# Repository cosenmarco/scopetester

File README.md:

# ScopeTester
An Open Hardware project for a small oscilloscope tester and calibrator with features like the [Hameg HZ-60](https://www.radiomuseum.org/r/hameg_scope_tester_hz_60.html).

## License
This project aims to be "open" in the sense of [Open Hardware](https://en.wikipedia.org/wiki/Open-source_hardware) and [Free Libre Open Source](https://en.wikipedia.org/wiki/Free_and_open-source_software).
The project is made available under the terms of the [Creative Commons license](https://creativecommons.org/licenses/by-sa/4.0/).

## Tools
The harware is developed using [KiCAD](http://kicad-pcb.org/).
Firmware is developed using [MPLAB X](http://www.microchip.com/mplab/mplab-x-ide) and the [XC8 compiler](http://www.microchip.com/mplab/compilers) from Microchip.

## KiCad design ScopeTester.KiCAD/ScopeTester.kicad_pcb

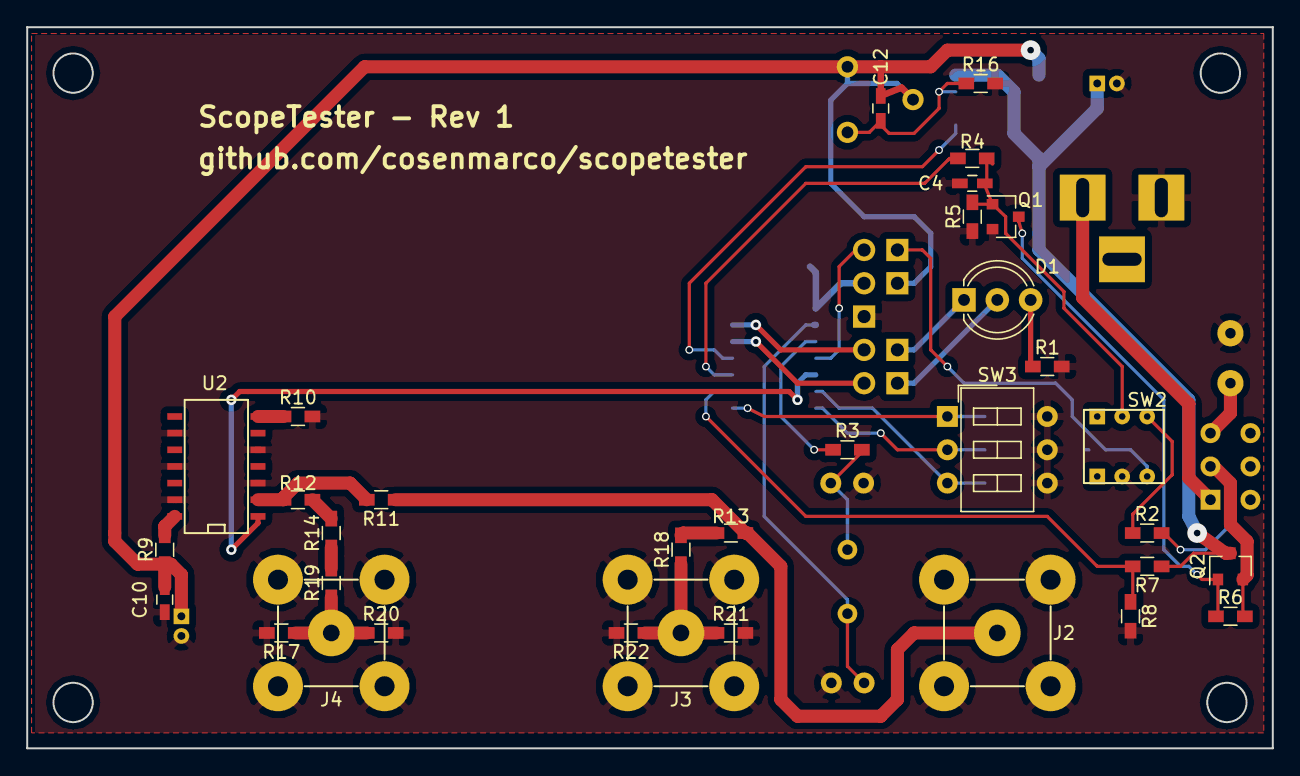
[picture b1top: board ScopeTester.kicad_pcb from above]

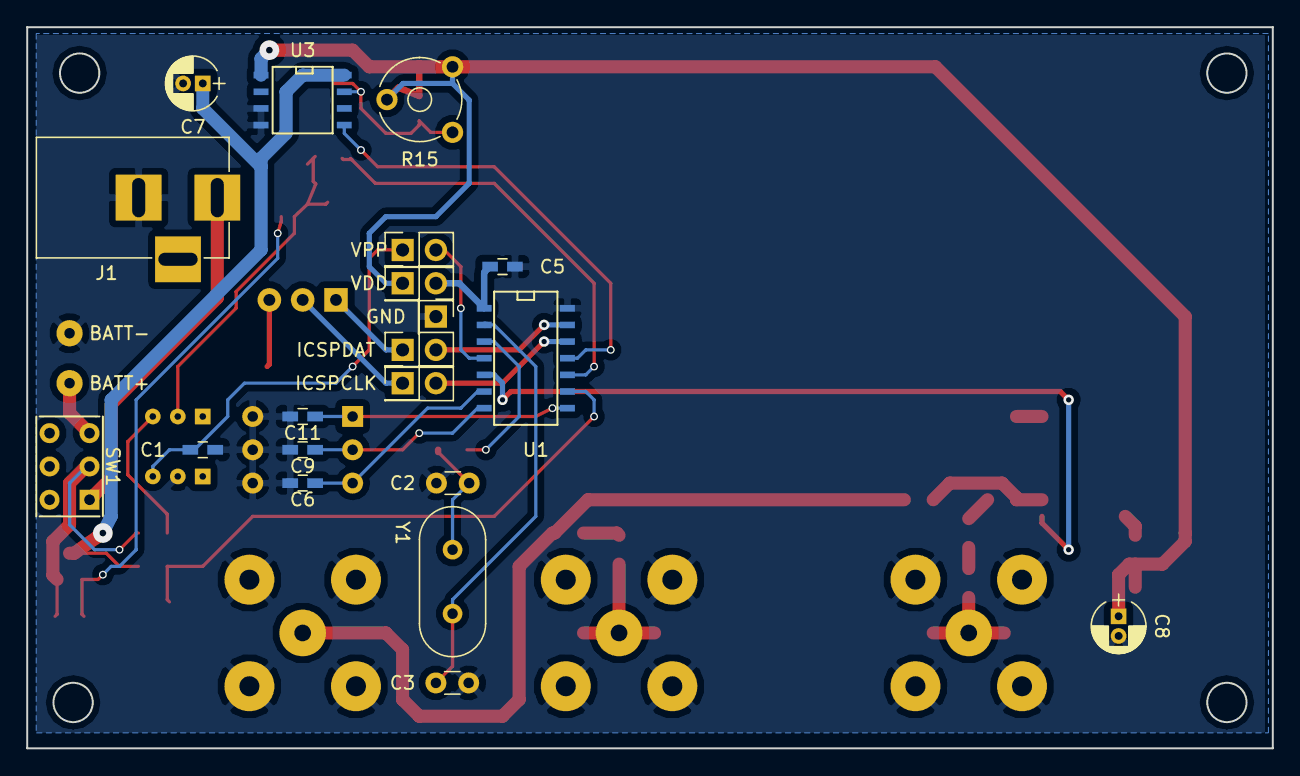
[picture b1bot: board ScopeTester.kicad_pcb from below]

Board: 2 copper layers, 95.0 x 55.0 mm, 55 parts (22 on the bottom side), 37 nets.

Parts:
BATT+: 4xLR6(AA); SolderWirePad_single_0-8mmDrill
BATT-: TEST; SolderWirePad_single_0-8mmDrill
C1: 330nF; C_0603_HandSoldering
C2, C3: 22pF; C_Disc_D3.0mm_W1.6mm_P2.50mm
C4: 0.22µF; C_0603_HandSoldering
C5: 100nF; C_0603_HandSoldering
C6, C9, C11: 0; C_0603_HandSoldering
C7: 3.3µF; CP_Radial_D4.0mm_P1.50mm
C8: 10µF; CP_Radial_D4.0mm_P1.50mm
C10, C12: 0.01µF; C_0603_HandSoldering
D1: ON/ERROR; LED_D5.0mm-3
GND: GND; Pin_Header_Straight_1x01_Pitch2.54mm
ICSPCLK: Jumper; Pin_Header_Straight_2x01_Pitch2.54mm
ICSPDAT: Jumper; Pin_Header_Straight_2x01_Pitch2.54mm
J1: 5VDC; BARREL_JACK
J2: 2.5Vpp; bnc-ci-large
J3: 250mV; bnc-ci-large
J4: 25mVpp into 50 Ohm; bnc-ci-large
Q1: BSS138; SOT-23
Q2: IRLML6401; SOT-23
R1: 560R; R_0603_HandSoldering
R2: 10K; R_0603_HandSoldering
R3: 0R; R_0603_HandSoldering
R4: 5K6; R_0603_HandSoldering
R5, R6: 56K; R_0603_HandSoldering
R7: 33k; R_0603_HandSoldering
R8: 12k; R_0603_HandSoldering
R9, R10: 15R; R_0603_HandSoldering
R11, R18: 150R; R_0603_HandSoldering
R12: 226R; R_0603_HandSoldering
R13: 301R; R_0603_HandSoldering
R14, R19: 1K5; R_0603_HandSoldering
R15: 220K; Potentiometer_Trimmer_Piher_PT-6v_Horizontal
R16: 100K; R_0603_HandSoldering
R17, R20, R21, R22: 100R; R_0603_HandSoldering
SW1: BATTERY/DC; SW_DPDT_Slide_mini
SW2: ON/OFF; DPDT_Button_mini
SW3: FREQ SEL; SW_DIP_x3_W7.62mm_Slide_LowProfile
U1: PIC16F1823-I/ST; SOIC-14_N
U2: 74AC14; SOIC-14_N
U3: TS2951; SOIC-8-N
VDD: Jumper; Pin_Header_Straight_2x01_Pitch2.54mm
VPP: Jumper; Pin_Header_Straight_2x01_Pitch2.54mm
Y1: 8.000Mhz; Crystal_HC49-4H_Vertical

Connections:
ERR: U1.11, U3.5
GND: BATT-.1, C1.2, C2.2, C3.2, C4.2, C5.1, C6.2, C7.2, C8.2, C9.2, C10.2, C11.2, GND.1, J1.2, J2.2, J3.2, J4.2, Q1.2, R1.2, R5.1, R8.2, R10.2, R16.2, R17.2, R20.2, R21.2, R22.2, SW2.5, SW3.4, SW3.5, SW3.6, U1.14, U2.3, U2.5, U2.9, U2.11, U2.13, U3.3, U3.4
unnamed: BATT+.1, SW1.3
unnamed: C2.1, R3.2, Y1.1
unnamed: C3.1, U1.2, Y1.2
unnamed: C4.1, Q1.1, R4.1, R5.2, SW2.2
unnamed: C5.2, U1.1, VDD.2
unnamed: C6.1, SW3.3, U1.6
unnamed: C7.1, Q2.3, R7.1, U3.8
unnamed: C9.1, SW3.2, U1.7
unnamed: C11.1, SW3.1, U1.8
unnamed: C12.2, R15.3, R16.1, U3.7
unnamed: D1.1, ICSPDAT.1
unnamed: D1.2, ICSPCLK.1
unnamed: D1.3, R1.1
unnamed: J1.1, SW1.1
unnamed: J2.1, R11.1, R13.2
unnamed: J3.1, R18.1, R21.1, R22.1
unnamed: J4.1, R17.1, R19.1, R20.1
unnamed: ICSPDAT.2, U1.13
unnamed: ICSPCLK.2, U1.12
unnamed: U1.4, VPP.2
unnamed: Q1.3, Q2.1, R6.1
unnamed: Q2.2, R2.2, R6.2, SW1.2
unnamed: R2.1, SW2.3
unnamed: R3.1, U1.3
unnamed: R9.2, U2.14
unnamed: R10.1, U2.7
unnamed: R11.2, R12.2, U2.2
unnamed: R12.1, R14.2
unnamed: R13.1, R18.2
unnamed: R14.1, R19.2
unnamed: U1.5, U2.1
SENSE: R7.2, R8.1, U1.9
SHUTDOWN: R4.2, U1.10
SWITCH: C1.1, SW2.6, VPP.1
VDD: C8.1, C10.1, C12.1, R9.1, R15.1, R15.2, U3.1, VDD.1

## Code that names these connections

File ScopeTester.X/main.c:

/**
 * Scope Tester
 * Author: https://github.com/cosenmarco
 * License: https://creativecommons.org/licenses/by-sa/4.0/legalcode
 * Processor: PIC16F1823
 * This is the C (Microchip XC8 compiler) source for the project discussed at 
 * http://www.eevblog.com/forum/projects/oscilloscope-tester-like-hameg-hz60/
*/
#include <xc.h>
#include <stdint.h>

// CONFIG1
#pragma config FOSC = HS        // Oscillator Selection (HS Oscillator, High-speed crystal/resonator connected between OSC1 and OSC2 pins)
#pragma config WDTE = OFF       // Watchdog Timer Enable (WDT disabled)
#pragma config PWRTE = ON       // Power-up Timer Enable (PWRT enabled)
#pragma config MCLRE = OFF      // MCLR Pin Function Select (MCLR/VPP pin function is digital input)
#pragma config CP = OFF         // Flash Program Memory Code Protection (Program memory code protection is disabled)
#pragma config CPD = OFF        // Data Memory Code Protection (Data memory code protection is disabled)
#pragma config BOREN = ON       // Brown-out Reset Enable (Brown-out Reset enabled)
#pragma config CLKOUTEN = OFF   // Clock Out Enable (CLKOUT function is disabled. I/O or oscillator function on the CLKOUT pin)
#pragma config IESO = OFF       // Internal/External Switchover (Internal/External Switchover mode is disabled)
#pragma config FCMEN = OFF      // Fail-Safe Clock Monitor Enable (Fail-Safe Clock Monitor is disabled)

// CONFIG2
#pragma config WRT = OFF        // Flash Memory Self-Write Protection (Write protection off)
#pragma config PLLEN = ON       // PLL Enable (4x PLL enabled) -- Fosc will be 32MHz with our 8MHz crystal
#pragma config STVREN = ON      // Stack Overflow/Underflow Reset Enable (Stack Overflow or Underflow will cause a Reset)
#pragma config BORV = LO        // Brown-out Reset Voltage Selection (Brown-out Reset Voltage (Vbor), low trip point selected.)
#pragma config LVP = OFF        // Low-Voltage Programming Enable (Low-voltage programming disabled)

// OUTPUTS
#define LED_GRN LATAbits.LATA0
#define LED_RED LATAbits.LATA1
#define SHUTDOWN LATCbits.LATC0
#define OUT LATCbits.LATC5

// INPUTS
#define ERR PORTAbits.RA2
#define SWITCH PORTAbits.RA3
#define SENSE PORTCbits.C12IN1N
#define FSEL0 PORTCbits.RC2
#define FSEL1 PORTCbits.RC3
#define FSEL2 PORTCbits.RC4

#define SW_PRESSED 0
#define SW_RELEASED 1

#define SHTDN_KEEP_ON 1
#define SHTDN_TURN_OFF 0

#define DC_OUT_LEVEL 0

typedef enum { 
    F_1MHz,
    F_100KHz,
    F_10KHz,
    F_1KHz,
    F_100Hz,
    F_10Hz,
    F_1Hz,
    F_DC
} mode_t;

typedef struct {
    unsigned char prescale;
    unsigned char pr2Value;
    unsigned char ccpr1lValue;
    unsigned char dc1bValue;
} pwm_setup_t;

typedef struct {
    unsigned char prescale;
    unsigned char ccpr1hValue;
    unsigned char ccpr1lValue;
} compare_setup_t;

void turnOnGreenLed(void);
void turnOnRedLed(void);
unsigned readMode(void);
void setupMode(mode_t mode);
void setupPWM(pwm_setup_t setup);
void setupCompare(compare_setup_t setup);
void setupDC(void);
void checkPower(void);

void main(void) {
    
    INTCONbits.GIE = 1; // Enable global interrupt
    INTCONbits.PEIE = 1; // Enable peripheral interrupt
    
    // PORT A configuration
    PORTA = 0;
    ANSELA = 0;
    TRISA = 0b111100; // Input from the TS2951 Error pin and the ON/OFF button
    WPUA = 0b001100; // Weak Pull-up enalbed on ERR and SWITCH inputs
    
    // PORT C configuration
    PORTC = 0;
    ANSELC = 0;
    TRISC = 0b011110; // We use here RC0 for SHUTDOWN and RC5 as the signal OUT
    WPUC = 0b011100; // We want to pull-up all the frequency seletion switches

    OPTION_REGbits.nWPUEN = 0; // Enable Weak Pull-up resistors
   
    SHUTDOWN = SHTDN_KEEP_ON; // Make sure circuit stays ON
    
    // Setup FVR and Comparator for battery voltage sensing
    FVRCON = 0b10000100; // Fixed Voltage Reference is enabled (1x)
    CM1CON0 = 0b10000010; // Enable Comparator (direct, low speed, hysteresis)
    CM1CON1 = 0b00100001; // No INT, + on FVR, - on C12IN1-

    // Setup Timer0 to blink the red led if necessary
    OPTION_REGbits.TMR0CS = 0; // Fosc/4 (8MHz)
    OPTION_REGbits.PSA = 0; // Prescaler ON
    OPTION_REGbits.PS = 0b111; // Prescale at 256
    
    turnOnGreenLed();

    mode_t mode = F_DC;
    mode_t oldmode = F_DC;
    
    setupMode(F_DC);

    // Given how the circuit boots, it is expected that upon startup the
    // SWITCH is pressed. Do nothing until the user releases it.
    while(SWITCH == SW_PRESSED) continue;

    do {        
        checkPower();
        mode = readMode();
        if(mode != oldmode) {
            oldmode = mode;
            setupMode(mode);
        }
    } while(SWITCH == SW_RELEASED);
    
    // Do nothing while the user keeps the switch pressed
    while(SWITCH == SW_PRESSED) continue;
    
    // User released ON/OFF. Shutdown now.
    setupMode(F_DC);
    SHUTDOWN = SHTDN_TURN_OFF; // Turn off power supply
    while(1); // Wait forever.
}

void turnOnGreenLed(void) {
    LED_GRN = 1;
    LED_RED = 0;
}

void turnOnRedLed(void) {
    LED_GRN = 0;
    LED_RED = 1;
}

void toggleRedLed(void) {
    LED_GRN = 0;
    LED_RED = ~LED_RED;
}

unsigned readMode() {
    return (unsigned) ((FSEL2 << 2) + (FSEL1 << 1) + FSEL0);
}

// Values obtained for a Fosc = 32MHz
const pwm_setup_t pwm_setup[] = {
    // Prescale,   PR2,      CCPR1L,  CCP1CON
    {      0b00,     7,       0b100,     0b00  }, // F_1MHz
    {      0b00,    79,    0b101000,     0b00  }, // F_100KHz
    {      0b01,   199,   0b1100100,     0b00  }, // F_10KHz
    {      0b11,   124,    0b111110,     0b10  }  // F_1KHz
};

// Values obtained for a Fosc = 32MHz
const compare_setup_t compare_setup[] = {
// Prescale,  CCPR1H,  CCPR1L
    {  0b00,    0x0F,    0xA0 }, // F_100Hz: Every 4000 (0xFA0) counts
    {  0b00,    0x9C,    0X40 }, // F_10Hz: Every 40000 (0x9C40) counts
    {  0b11,    0XC3,    0x50 }  // F_1Hz: Every 50000 (0xC350) counts
};

/**
 * Sets up the operating frequency which will be generated at pin OUT.
 * The modes F_1MHz to F_1KHz use the PWM module according to the config
 * table stored in pwm_setup.
 * The modes F_100Hz to F_1Hz use the Compare mode to generate an interrupt
 * at different frequencies. The ISR will always divide this frequency by
 * 10, so this must be taken into account in the setup of Timer1 and CCPR1.
 * Clocking Timer1 from the system clock (F OSC ) should not be used in Compare
 * mode. This means Fosc/4 is 8MHz
 * @param mode The chosen operating mode
 */
void setupMode(mode_t mode) {
    setupDC(); // Reset everything and provide default

    switch(mode) {
        case F_1MHz:
        case F_100KHz:
        case F_10KHz:
        case F_1KHz:
            setupPWM(pwm_setup[mode]);
            break;

        case F_100Hz:
        case F_10Hz:
        case F_1Hz:
            setupCompare(compare_setup[mode - F_100Hz]);
            break;
    }
}

void setupPWM(pwm_setup_t setup) {
    // Configure Timer2 and PWM
    T2CONbits.T2CKPS = setup.prescale;
    PR2 = setup.pr2Value;
    CCPR1L = setup.ccpr1lValue;
    CCP1CONbits.DC1B = setup.dc1bValue;
    TMR2 = 0xFF;

    // Start Timer2 and PWM
    CCP1CONbits.CCP1M = 0b1100; // PWM mode: P1A, P1C active-high; P1B, P1D active-high
    T2CONbits.TMR2ON = 1;
}

void setupCompare(compare_setup_t setup) {
    PIE1bits.CCP1IE = 1; // Enables the CCP1 interrupt
    CCP1CONbits.CCP1M = 0b1010; // Compare mode: generate software interrupt only
    T1CONbits.TMR1CS = 0b00; // Fosc/4 (8MHz)
    T1CONbits.T1CKPS = setup.prescale;
    CCPR1H = setup.ccpr1hValue;
    CCPR1L = setup.ccpr1lValue;
    T1CONbits.TMR1ON = 1; // Turn ON Timer1
}

void setupDC() {
    CCP1CONbits.CCP1M = 0; // Capture/Compare/PWM off (resets ECCP1 module)
    OUT = DC_OUT_LEVEL; // Set OUT to the correct logic level to have a pure DC output

    // Turn OFF and reset Timer1
    T1CONbits.TMR1ON = 0;
    TMR1L = 0;
    TMR1H = 0;

    T2CONbits.TMR2ON = 0; // Turn off Timer2
    PIE1bits.CCP1IE = 0; // Disables the CCP1 interrupt
}

unsigned char blinkState = 0;
void checkPower() {
    if (!ERR) { // ERR is active LOW
        if (INTCONbits.T0IF) {
            INTCONbits.T0IF = 0; // Clear interrupt bit
            if (++blinkState > 50) {
                blinkState = 0;
                toggleRedLed();
            }
        }
    } else {
        blinkState = 0;
        if (FVRCONbits.FVRRDY && CM1CON0bits.C1OUT) { 
            turnOnRedLed();
        } else {
            turnOnGreenLed();
        }
    }
}
               
volatile unsigned char ocState = 0;
void interrupt isr(void) {
    if (PIR1bits.CCP1IF) {
        PIR1bits.CCP1IF = 0; // Clear interrupt bit
        
        // Resets the Timer1
        TMR1H = 0;
        TMR1L = 0;

        // Every 10 calls toogle the OUT pin
        if (++ocState >= 10) {
            ocState = 0;
            OUT = ~OUT;
        }
    }    
}

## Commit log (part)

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2017-11-05 Project in Github
2017-11-05 Adding README
2017-11-05 Improved README
2017-11-10 Using PWM mode or higher frequencies
2017-11-11 Adding led management code and editorconfig
2017-12-12 Fixing a few small issues
2018-03-11 Adding PCB Rev 1
2018-04-05 Hopefully fixing missing libraries issue at .sch loading

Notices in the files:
README.md:
License: CC BY-SA 4.0
